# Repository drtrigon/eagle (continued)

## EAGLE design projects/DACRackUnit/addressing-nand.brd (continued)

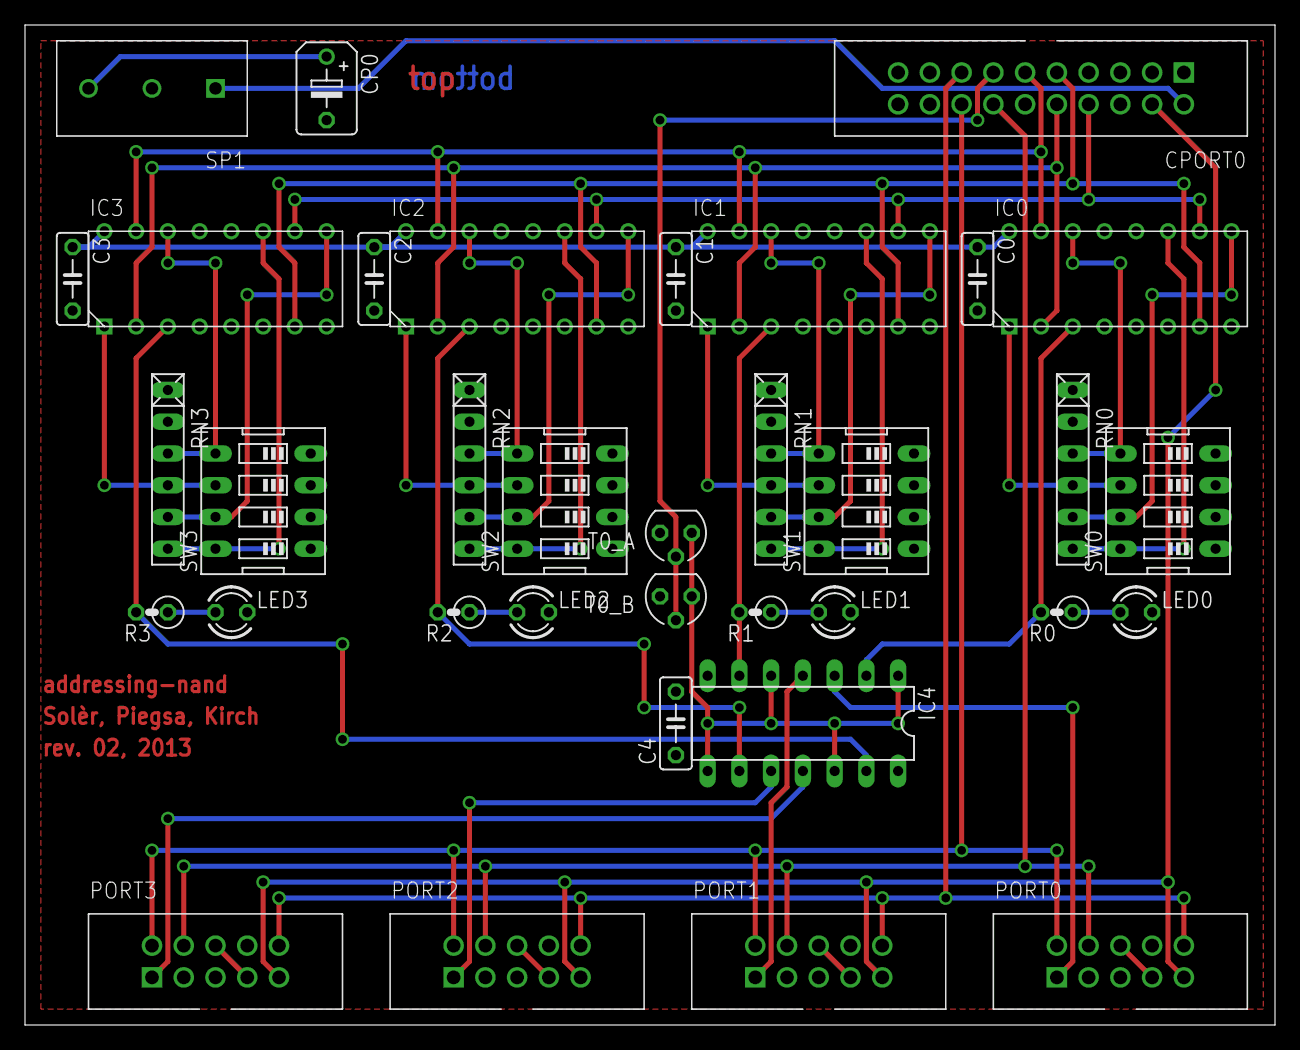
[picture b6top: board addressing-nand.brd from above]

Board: 2 copper layers, 100.0 x 80.0 mm, 35 parts (0 on the bottom side), 41 nets.

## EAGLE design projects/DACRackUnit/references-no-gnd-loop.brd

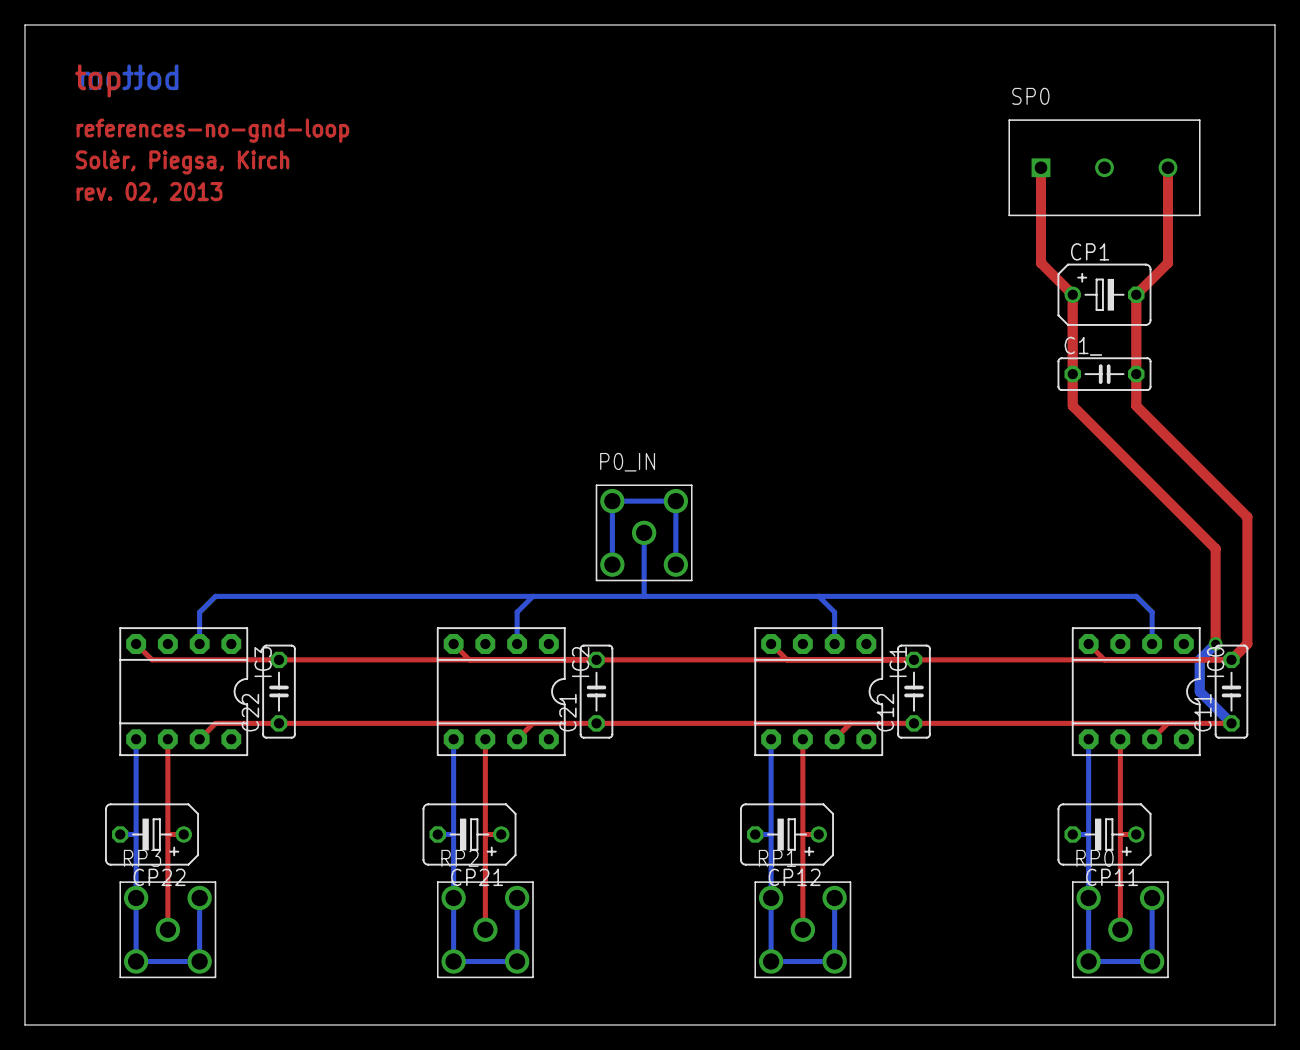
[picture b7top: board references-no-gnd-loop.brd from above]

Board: 2 copper layers, 100.0 x 80.0 mm, 20 parts (0 on the bottom side), 12 nets.

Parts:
C1_, C11, C12, C21, C22: 100nF; C050-025X075
CP1: 10uF; B45181B
CP11, CP12, CP21, CP22: 2.2uF; B45181B
IC0, IC1, IC2, IC3: INA118P; DIL08
P0_IN: SMB-50OHM; B-30
RP0, RP1, RP2, RP3: SMB-50OHM; B-30
SP0: WAGO-3

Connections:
+15V: C1_.1, C11.1, C12.1, C21.1, C22.1, CP1.+, IC0.7, IC1.7, IC2.7, IC3.7, SP0.P$1
+V1: IC0.2, IC1.2, IC2.2, IC3.2, P0_IN.P$1
-15V: C1_.2, C11.2, C12.2, C21.2, C22.2, CP1.-, IC0.4, IC1.4, IC2.4, IC3.4, SP0.P$3
GND: IC0.3, IC1.3, IC2.3, IC3.3, P0_IN.P$2, P0_IN.P$3, P0_IN.P$4, P0_IN.P$5
RGND0: CP11.-, IC0.5, RP0.P$2, RP0.P$3, RP0.P$4, RP0.P$5
RGND1: CP12.-, IC1.5, RP1.P$2, RP1.P$3, RP1.P$4, RP1.P$5
RGND2: CP21.-, IC2.5, RP2.P$2, RP2.P$3, RP2.P$4, RP2.P$5
RGND3: CP22.-, IC3.5, RP3.P$2, RP3.P$3, RP3.P$4, RP3.P$5
VOUT0: CP11.+, IC0.6, RP0.P$1
VOUT1: CP12.+, IC1.6, RP1.P$1
VOUT2: CP21.+, IC2.6, RP2.P$1
VOUT3: CP22.+, IC3.6, RP3.P$1

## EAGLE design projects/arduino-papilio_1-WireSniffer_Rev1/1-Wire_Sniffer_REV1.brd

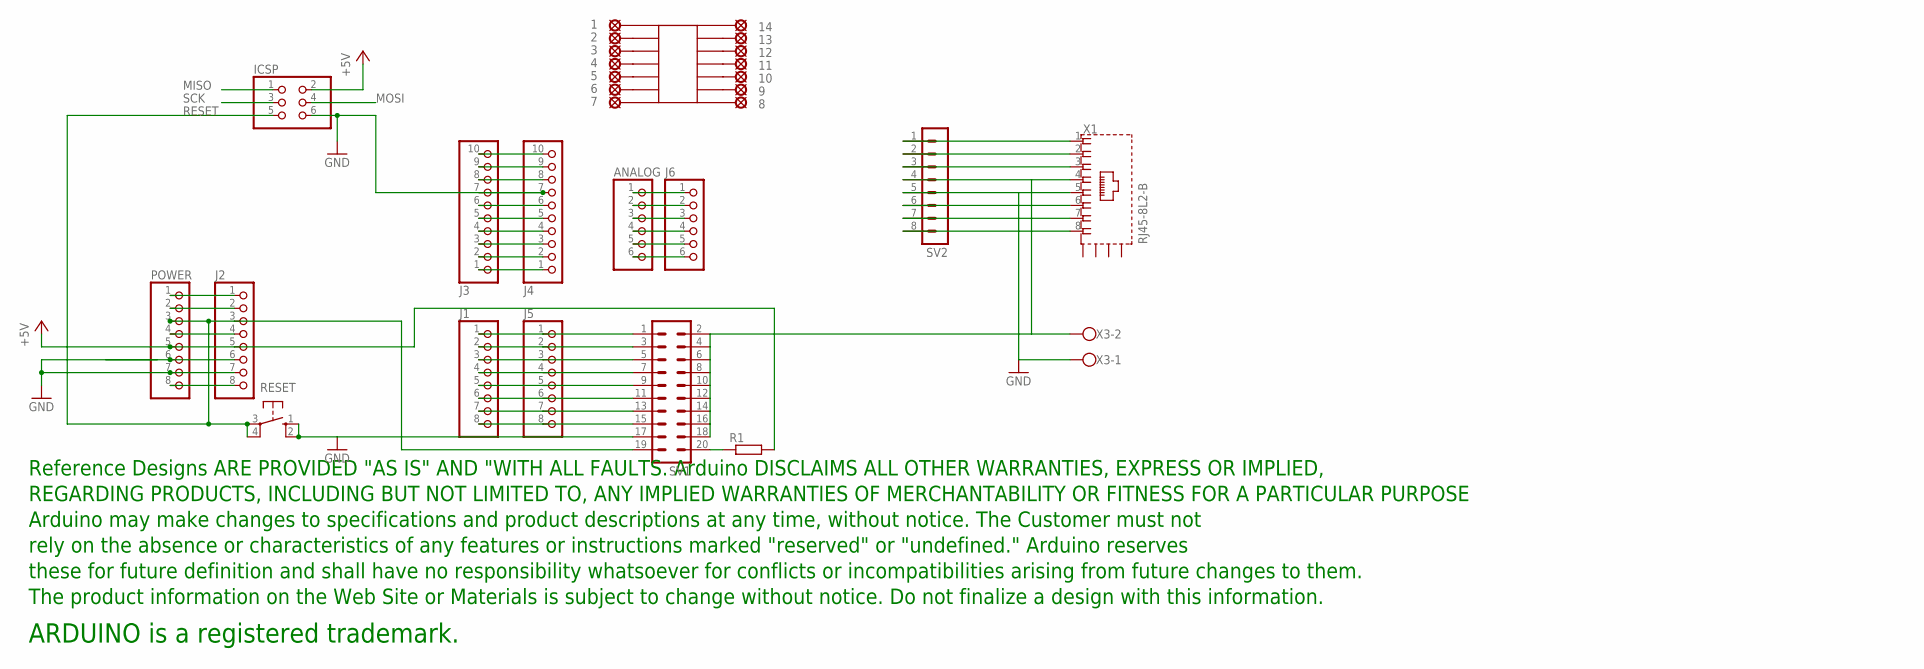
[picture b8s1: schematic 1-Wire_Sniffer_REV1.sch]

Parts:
1, 2, 3, 4, 5, 6, 7, 8, 9, 10, 11, 12, 13, 14: LSP10
ANALOG: PINHD-1X6; 1X06
IC2: SMD-14; SO-14NMW
ICSP: PINHD-2X3; 2X03
J1, J2, J5: PINHD-1X8TH; 1X08-TH
J3, J4: PINHD-1X10TH; 1X10-TH
J6: PINHD-1X6; 1X06
POWER: PINHD-1X8TH; 1X08-TH
R1: R-EU_0207/10; 0207/10
RESET: 10-XX; B3F-10XX
SV1: MA10-2
SV2: MA08-1
U$1: DISCLAIMER
X1: RJ45-8L2-B; RJ45-SHIELD2
X3: W237-102

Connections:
+5V: ICSP.2, J2.5, POWER.5, R1.2
+9V: J2.8, POWER.8
GND: ICSP.6, J2.7, J3.7, J4.7, POWER.7, RESET.1 (S), RESET.2 (S1), SV1.17, SV2.5, X1.5, X3.1
MISO: ICSP.1
MOSI: ICSP.4
unnamed: J3.6, J4.6
unnamed: J3.1, J4.1
unnamed: J3.4, J4.4
unnamed: J3.5, J4.5
unnamed: SV1.2, SV1.4, SV1.6, SV1.8, SV1.10, SV1.12, SV1.14, SV1.16, SV1.18, SV2.4, X1.4, X3.2
unnamed: J3.2, J4.2
unnamed: J3.3, J4.3
unnamed: J1.1, J5.1, SV1.1
unnamed: J1.2, J5.2, SV1.3
unnamed: J1.3, J5.3, SV1.5
unnamed: J1.4, J5.4, SV1.7
unnamed: J1.5, J5.5, SV1.9
unnamed: J1.6, J5.6, SV1.11
unnamed: J1.7, J5.7, SV1.13
unnamed: J1.8, J5.8, SV1.15
unnamed: SV2.1, X1.1
unnamed: SV2.2, X1.2
unnamed: ANALOG.1, J6.1
unnamed: ANALOG.2, J6.2
unnamed: ANALOG.3, J6.3
unnamed: ANALOG.4, J6.4
unnamed: ANALOG.5, J6.5
unnamed: ANALOG.6, J6.6
unnamed: 14.MP, IC2.P$14
unnamed: SV2.3, X1.3
unnamed: J2.2, POWER.2
unnamed: J2.1, POWER.1
unnamed: SV2.6, X1.6
unnamed: SV2.7, X1.7
unnamed: SV2.8, X1.8
unnamed: 13.MP, IC2.P$13
unnamed: 12.MP, IC2.P$12
unnamed: 11.MP, IC2.P$11
unnamed: 10.MP, IC2.P$10
unnamed: 9.MP, IC2.P$9
unnamed: 8.MP, IC2.P$8
unnamed: 7.MP, IC2.P$7
unnamed: 6.MP, IC2.P$6
unnamed: 5.MP, IC2.P$5
unnamed: 3.MP, IC2.P$3
unnamed: 2.MP, IC2.P$2
unnamed: 1.MP, IC2.P$1
unnamed: 4.MP, IC2.P$4
unnamed: J3.9, J4.9
unnamed: J3.10, J4.10
unnamed: R1.1, SV1.20
unnamed: J2.6, POWER.6
unnamed: J3.8, J4.8
unnamed: J2.4, POWER.4
RESET: ICSP.5, J2.3, POWER.3, RESET.3, RESET.4 (P1), SV1.19
SCK: ICSP.3

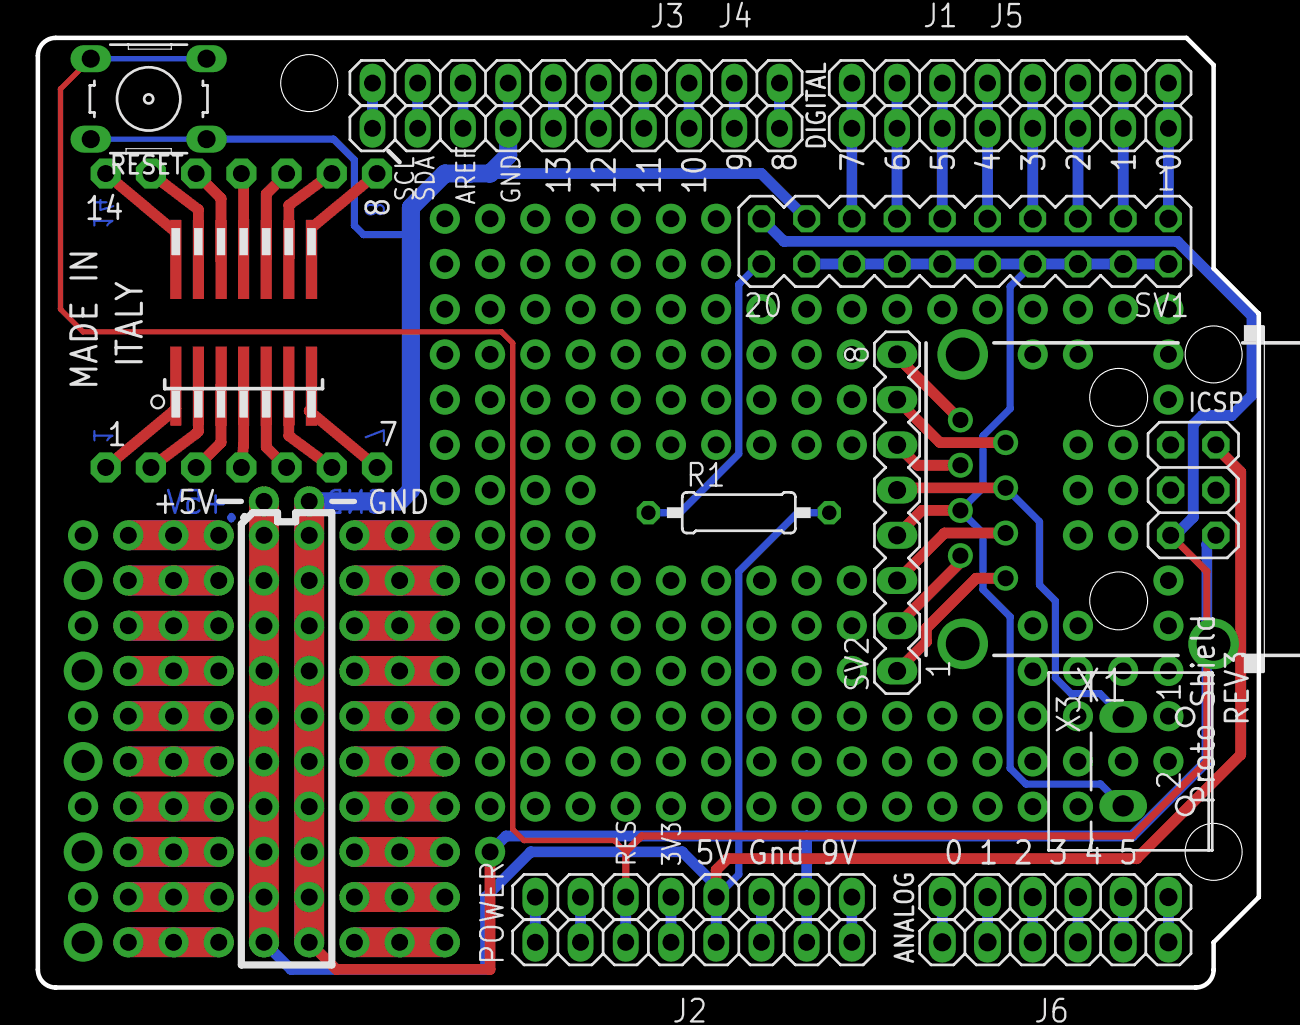
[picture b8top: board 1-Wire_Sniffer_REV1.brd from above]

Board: 2 copper layers, 68.6 x 53.3 mm, 31 parts (0 on the bottom side), 53 nets.

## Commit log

2018-03-24 Initialer Commit
2018-03-24 improvement; * additional libraries (Arduino Nano, connectors) * added link to JLCPCB (very cheap)
2018-03-25 improvement; * add how to config eagle directories
2018-04-07 new feature; * add edrc.me support for pcb
2018-04-07 improvement; * minor docu changes
2018-04-07 bugfix; * added config file edrc.yml
2018-04-07 improvement; * add correct pcb image
2018-04-07 bugfix; * correct link to other repo
2018-04-07 bugfix; * wrong path in docu * minor sytle fixes
2018-04-13 new feature; * enable gerber file creation on travis
2018-04-13 clean-up; * omitt ls -la as switching branch does the same * add links and info
2018-04-13 clean-up; * minor typo fixed
2018-04-14 new feature; * enable mill&drill support for gerber and png
2018-04-14 follow-up; * go back to default gerber (no mill&drill) as sequence needs adoption
2018-04-14 improvement; * make gerber with mill&drill working, automate process
2018-04-14 improvement; * add re-focussing step * clean-up
2018-04-14 clean-up; * revert to non-mill&drill
2018-04-14 clean-up; * delete obsolete files * rename old gerber zip
2018-04-14 new feature; * generate gerber view png of top and bottom layer
2018-04-15 bugfix; * add new files to git
2018-04-15 improvement; * add drill (excellon) data to gerber view
2018-04-15 bugfix; * got back and omitt drill file
2018-04-15 improvement; * add --antialias for gerber creation
2018-04-17 improvement; * rename result branch
2018-04-19 new features; * enable schematic, board, erc, drc, autorouter output
2018-04-20 clean-up; * minor docu changes
2018-04-20 new feature; * add license
2018-04-20 improvment; * enhance license with non-software stuff
2018-04-20 new feature; * add other projects to edrc.me
2018-04-20 improvement; * slightly re-group sections in docu
2018-04-20 clean-up; * minor changes to docu
2018-04-20 improvement; * remove arduino_ProtoShield_Rev3 folder in favor of a zip archive
2018-04-20 follow-up; * also remove links from docu
2018-04-28 improvement; * N64TinyUSB pcb added (moved here from sketchbook repo)
2018-05-01 improvement; * update N64TinyUSB (99% done) * add HelveTiny gerber files * add 3.3V-5V supply info datasheet * enable matrix processing in travis
2018-05-01 improvement; * try to keep history of travis commits
2018-05-01 clean-up; * finish travis config * use routed version of pcb
2018-05-01 improvement; * docu updated
2018-05-01 improvement; * switch gerber file back to default (no mill&drill) for compatibility with viewers and companies * move labeling from bottom to top layer
2018-05-01 improvement; * fix issue with .dri check (mill vs. no-mill) * enables at same time use of GERBER_CAM_FILE in matrix
2018-05-01 bugfix; * other logic to return non-zero codes in correct situation only
2018-05-01 improvement; * minor docu additions * add dimension labels to pcb * add diode datasheet
2018-05-01 improvement; * added sniffer - all (active/private) projects on travis now
2018-05-02 new feature; * eagle to kicad conversion test
2018-05-02 improvement; * add some comments
2018-05-02 bugfix; * add travis_wait to extend build run time
2018-05-02 follow-up; * bugfix was at wrong position
2018-05-02 bugfix; * get more output for debug
2018-05-02 improvement; * addition Tab before entering filename
2018-05-02 follow-up; * killall kicad * try Right key to select files
2018-05-03 follow-up; * more info for commit message and debug
2018-05-03 follow-up; * get more debug info
2018-05-03 follow-up; * try to naviagte the file open dialog
2018-05-03 follow-up; * try to naviagte with mouse
2018-05-03 follow-up; * file selection by mouse works (finally) * docu clean-up
2018-05-03 follow-up; * import works - try to store and close
2018-05-03 follow-up; * disable kicad except for FlightController
2018-05-03 follow-up; * minor docu additions * use mouse in pcbnew
2018-05-03 follow-up; * minor docu addition * use arrows instead of alt+char
2018-05-03 follow-up; * exit menu * test 2nd variant using ctrl+q for exit
2018-05-03 follow-up; * try to pack data into zip
2018-05-03 follow-up; * eagle2kicad works now ;))
2018-05-03 clean-up; * kicad works, finishing now
2018-05-03 improvement; * N64TinyUSB v1.0 sent for production to JLCPCB
2018-05-04 improvement; * converted eagle files from v6 (or earlier binary) to v7 (xml)
2018-05-04 improvement; * make eagle download more reliable (45 instead of 20 retries)
2018-05-04 improvement; * add results, as all checks on edrc.me work now
2018-05-04 Travis build 57 (374831260)
2018-05-04 improvement; * try to perserve branch history
2018-05-04 Travis build 58 (375095512)
2018-05-04 improvement; * kicad is now adaptive to env/matrix variables
2018-05-04 Travis build 59 (375113510)
2018-05-19 new feature; * add eagle-view github repo
2018-05-19 Travis build 60 (381043407)
2018-05-20 improvement; N64TinyUSB v1.1 * pol-cap position * text placement and size (2 parts, v1.1, date) * thermals width 5 * diode type 1N4150 * run tests and aprove 1 error
2018-05-20 Travis build 61 (381335258)
2018-08-21 migration; * import/convert add designs (schem, pcb) to KiCAD
2018-08-21 Travis build 62 (418567766)
2018-09-04 docu; * add hints/todo for KiCAD travis output generation and graphical diff
2019-01-23 new feature; * add URBBB atmega328 minimal board (V1, might need tuning)
2019-01-24 improvement; * add overview of jlcpcb orders done
2019-03-12 improvement; * add JLCPCB production images
2019-03-12 improvement; * tindie needs a minimal height, thus rotated
2019-03-17 improvement; * add production images (top view only)
